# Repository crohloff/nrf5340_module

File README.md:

# nRF5340 module
WIP

## features
- power path management (USB or battery connected)
- battery charging circuit 500mA charging current
- no expensive uVias

## board front

## board back

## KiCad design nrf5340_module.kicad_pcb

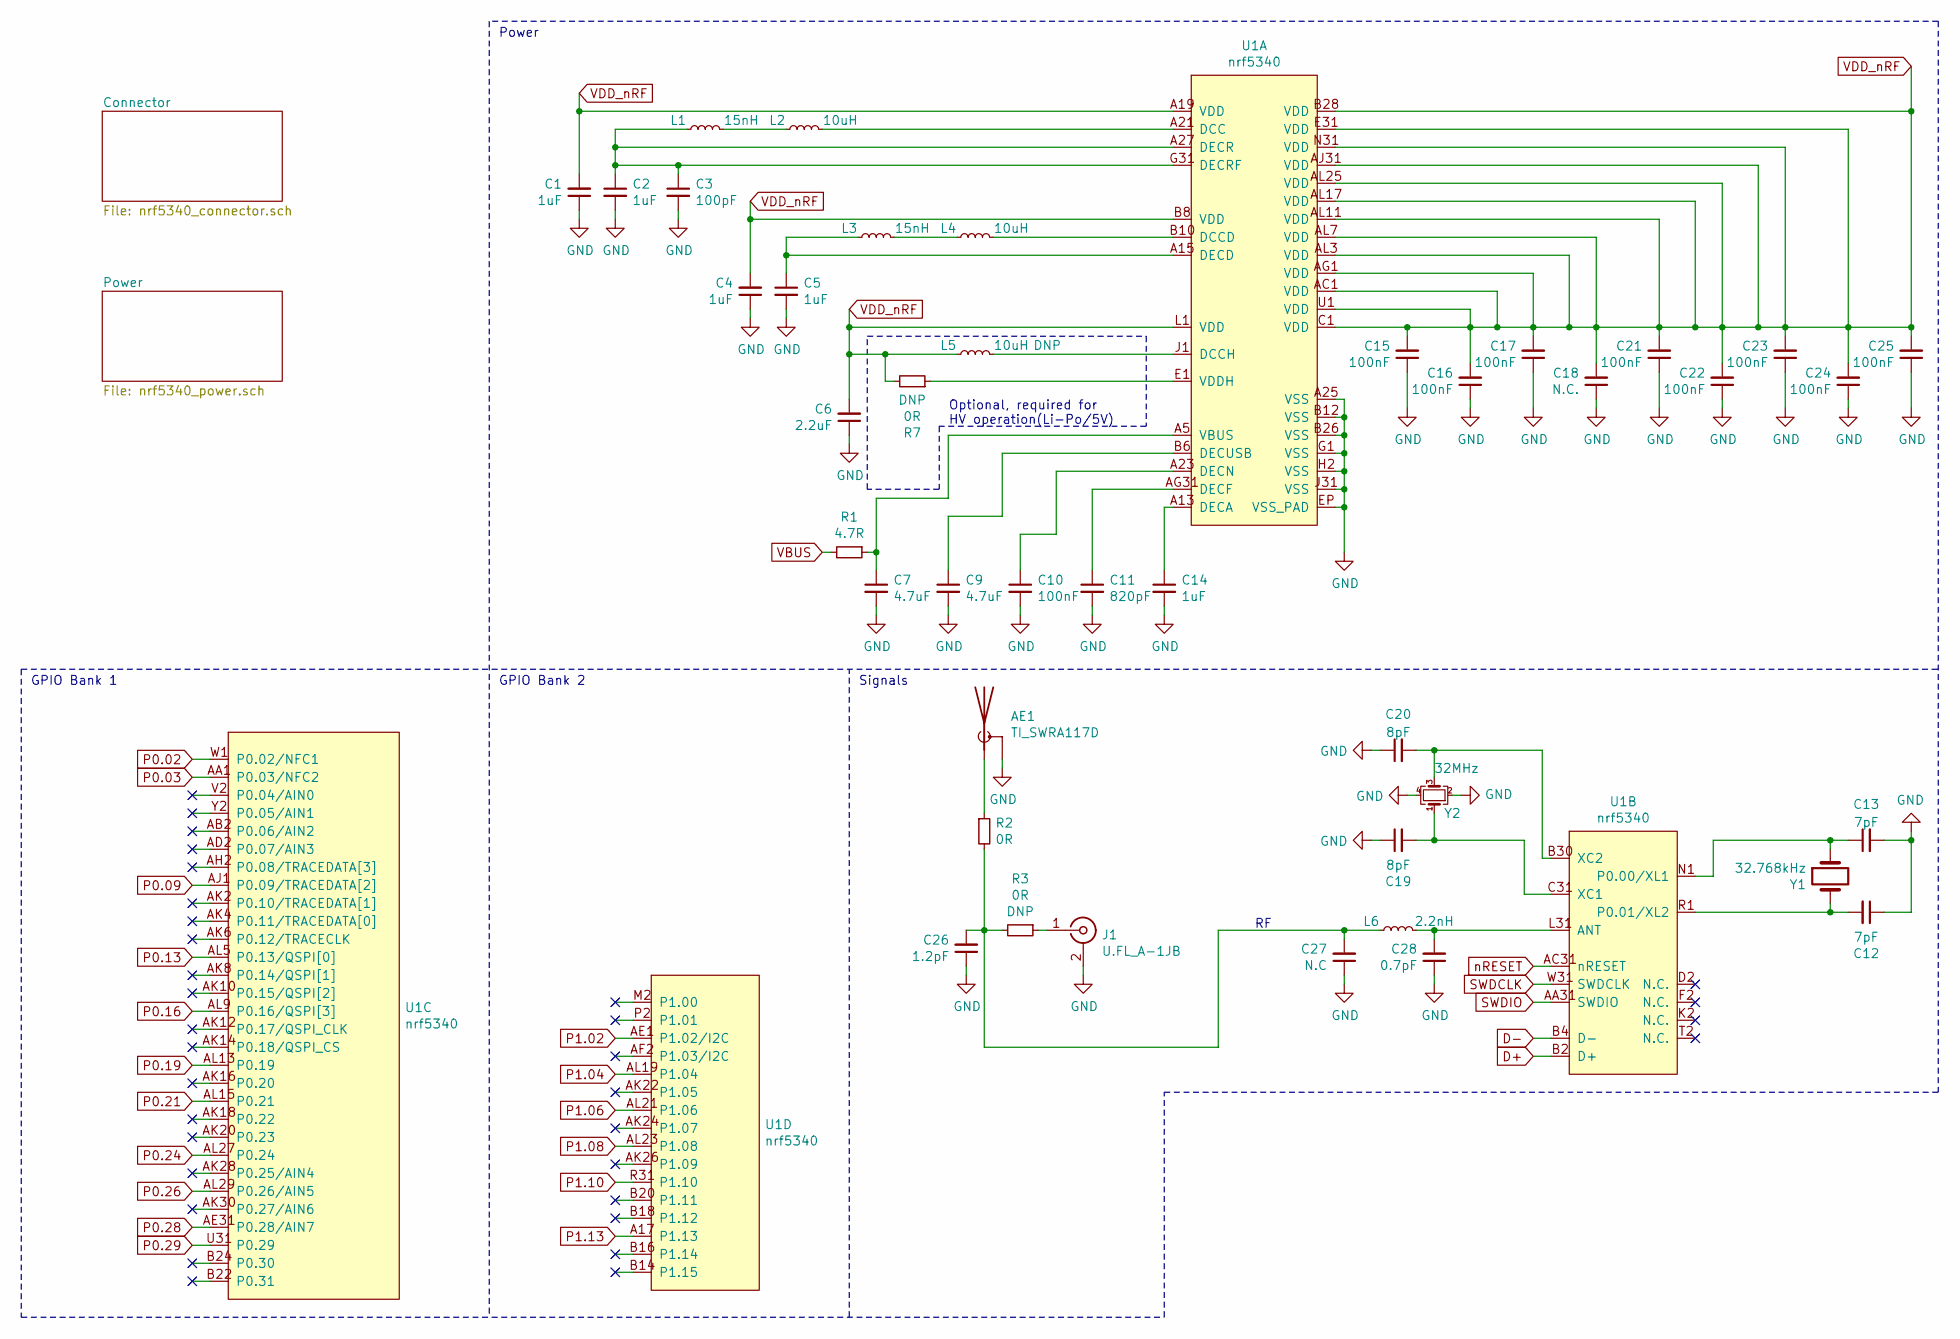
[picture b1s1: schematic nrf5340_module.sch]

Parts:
AE1: TI_SWRA117D; Texas_SWRA117D_2.4GHz_Right
C1, C2, C4, C5, C14: 1uF; C_0402_1005Metric
C3: 100pF; C_0201_0603Metric
C6: 2.2uF; C_0603_1608Metric
C7, C9: 4.7uF; C_0603_1608Metric
C10, C15, C16, C17, C21, C22, C23, C24, C25: 100nF; C_0201_0603Metric
C11: 820pF; C_0201_0603Metric
C12, C13: 7pF; C_0201_0603Metric
C18: N.C.; C_0201_0603Metric
C19, C20: 8pF; C_0201_0603Metric
C26: 1.2pF; C_0201_0603Metric
C27: N.C; C_0201_0603Metric
C28: 0.7pF; C_0201_0603Metric
J1: U.FL_A-1JB; CON_AMP_A-1JB
L1, L3: 15nH; L_0201_0603Metric
L2, L4, L5: 10uH; L_0603_1608Metric
L6: 2.2nH; L_0201_0603Metric
R1: 4.7R; R_0201_0603Metric
R2, R3: 0R; R_0201_0603Metric
R7: 0R; R_0603_1608Metric
U1: nrf5340; Nordic_AQFN-94-1EP_7x7mm_P0.4mm
Y1: 32.768kHz; Crystal_SMD_2012-2Pin_2.0x1.2mm
Y2: 32MHz; Crystal_SMD_2016-4Pin_2.0x1.6mm

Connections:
D+: U1.B2 (D+); also elsewhere on the board
D-: U1.B4 (D-); also elsewhere on the board
GND: AE1.2 (Shield), C1.1, C2.2, C3.2, C4.1, C5.2, C6.1, C7.2, C9.2, C10.2, C11.2, C12.1, C13.2, C14.2, C15.1, C16.1, C17.1, C18.1, C19.1, C20.1, C21.1, C22.1, C23.1, C24.1, C25.1, C26.1, C27.1, C28.1, J1.2 (Ext), U1.A25 (VSS), U1.B12 (VSS), U1.B26 (VSS), U1.EP (VSS_PAD), U1.G1 (VSS), U1.H2 (VSS), U1.J31 (VSS), Y2.2, Y2.4; also elsewhere on the board
unnamed: AE1.1 (A), R2.1
unnamed: C2.1, C3.1, L1.1, U1.A27 (DECR), U1.G31 (DECRF)
unnamed: C5.1, L3.1, U1.A15 (DECD)
unnamed: C7.1, R1.1, U1.A5 (VBUS)
unnamed: C9.1, U1.B6 (DECUSB)
unnamed: C10.1, U1.A23 (DECN)
unnamed: C11.1, U1.AG31 (DECF)
unnamed: C12.2, U1.R1 (P0.01/XL2), Y1.2
unnamed: C13.1, U1.N1 (P0.00/XL1), Y1.1
unnamed: C14.1, U1.A13 (DECA)
unnamed: C19.2, U1.C31 (XC1), Y2.1
unnamed: C20.2, U1.B30 (XC2), Y2.3
unnamed: C26.2, C27.2, L6.1, R2.2, R3.2
unnamed: C28.2, L6.2, U1.L31 (ANT)
unnamed: J1.1 (In), R3.1
unnamed: L1.2, L2.1
unnamed: L2.2, U1.A21 (DCC)
unnamed: L3.2, L4.1
unnamed: L4.2, U1.B10 (DCCD)
unnamed: L5.2, U1.J1 (DCCH)
unnamed: R7.1, U1.E1 (VDDH)
P0.02: U1.W1 (P0.02/NFC1); also elsewhere on the board
P0.03: U1.AA1 (P0.03/NFC2); also elsewhere on the board
P0.09: U1.AJ1 (P0.09/TRACEDATA[2]); also elsewhere on the board
P0.13: U1.AL5 (P0.13/QSPI[0]); also elsewhere on the board
P0.16: U1.AL9 (P0.16/QSPI[3]); also elsewhere on the board
P0.19: U1.AL13 (P0.19); also elsewhere on the board
P0.21: U1.AL15 (P0.21); also elsewhere on the board
P0.24: U1.AL27 (P0.24); also elsewhere on the board
P0.26: U1.AL29 (P0.26/AIN5); also elsewhere on the board
P0.28: U1.AE31 (P0.28/AIN7); also elsewhere on the board
P0.29: U1.U31 (P0.29); also elsewhere on the board
P1.02: U1.AE1 (P1.02/I2C); also elsewhere on the board
P1.04: U1.AL19 (P1.04); also elsewhere on the board
P1.06: U1.AL21 (P1.06); also elsewhere on the board
P1.08: U1.AL23 (P1.08); also elsewhere on the board
P1.10: U1.R31 (P1.10); also elsewhere on the board
P1.13: U1.A17 (P1.13); also elsewhere on the board
SWDCLK: U1.W31 (SWDCLK); also elsewhere on the board
SWDIO: U1.AA31 (SWDIO); also elsewhere on the board
VBUS: R1.2; also elsewhere on the board
VDD_nRF: C1.2, C4.2, C6.2, C15.2, C16.2, C17.2, C18.2, C21.2, C22.2, C23.2, C24.2, C25.2, L5.1, R7.2, U1.A19 (VDD), U1.AC1 (VDD), U1.AG1 (VDD), U1.AJ31 (VDD), U1.AL3 (VDD), U1.AL7 (VDD), U1.AL11 (VDD), U1.AL17 (VDD), U1.AL25 (VDD), U1.B8 (VDD), U1.B28 (VDD), U1.C1 (VDD), U1.E31 (VDD), U1.L1 (VDD), U1.N31 (VDD), U1.U1 (VDD); also elsewhere on the board
nRESET: U1.AC31 (nRESET); also elsewhere on the board

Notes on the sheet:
Optional, required for HV operation(Li-Po/5V)
GPIO Bank 1
GPIO Bank 2
Power
Signals

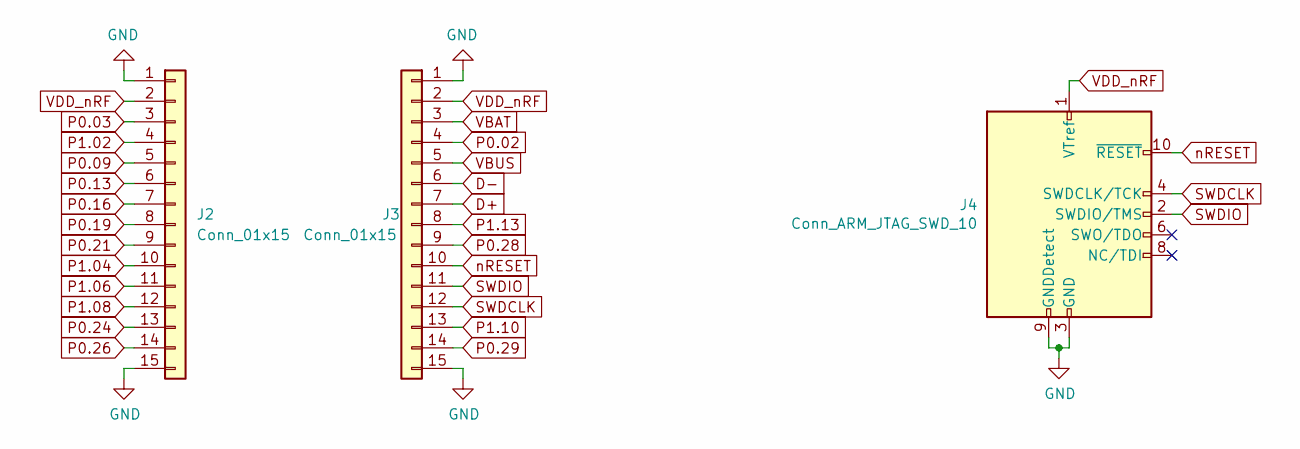
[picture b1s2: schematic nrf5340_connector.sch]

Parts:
J2, J3: Conn_01x15; PinHeader_1x15_P1.27mm_Vertical
J4: Conn_ARM_JTAG_SWD_10; PinHeader_2x05_P1.27mm_Vertical_SMD

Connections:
D+: J3.7; also elsewhere on the board
D-: J3.6; also elsewhere on the board
GND: J2.1, J2.15, J3.1, J3.15, J4.3 (GND), J4.5 (GND), J4.9 (GNDDetect); also elsewhere on the board
P0.02: J3.4; also elsewhere on the board
P0.03: J2.3; also elsewhere on the board
P0.09: J2.5; also elsewhere on the board
P0.13: J2.6; also elsewhere on the board
P0.16: J2.7; also elsewhere on the board
P0.19: J2.8; also elsewhere on the board
P0.21: J2.9; also elsewhere on the board
P0.24: J2.13; also elsewhere on the board
P0.26: J2.14; also elsewhere on the board
P0.28: J3.9; also elsewhere on the board
P0.29: J3.14; also elsewhere on the board
P1.02: J2.4; also elsewhere on the board
P1.04: J2.10; also elsewhere on the board
P1.06: J2.11; also elsewhere on the board
P1.08: J2.12; also elsewhere on the board
P1.10: J3.13; also elsewhere on the board
P1.13: J3.8; also elsewhere on the board
SWDCLK: J3.12, J4.4 (SWDCLK/TCK); also elsewhere on the board
SWDIO: J3.11, J4.2 (SWDIO/TMS); also elsewhere on the board
VBAT: J3.3; also elsewhere on the board
VBUS: J3.5; also elsewhere on the board
VDD_nRF: J2.2, J3.2, J4.1 (VTref); also elsewhere on the board
nRESET: J3.10, J4.10 (~RESET~); also elsewhere on the board

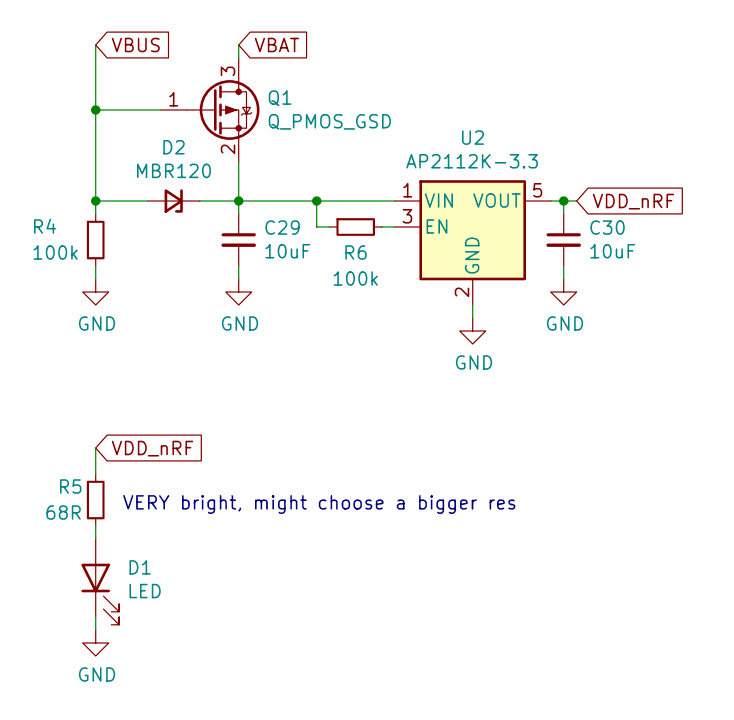
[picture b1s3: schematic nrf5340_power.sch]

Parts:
C29, C30: 10uF; C_0201_0603Metric
D1: LED; LED_0402_1005Metric
D2: MBR120; D_SOD-123
Q1: Q_PMOS_GSD; SOT-23
R4, R6: 100k; R_0201_0603Metric
R5: 68R; R_0201_0603Metric
U2: AP2112K-3.3; SOT-23-5

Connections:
GND: C29.2, C30.2, D1.1 (K), R4.2, U2.2 (GND); also elsewhere on the board
unnamed: C29.1, D2.1 (K), Q1.2 (S), R6.1, U2.1 (VIN)
unnamed: D1.2 (A), R5.2
unnamed: R6.2, U2.3 (EN)
VBAT: Q1.3 (D); also elsewhere on the board
VBUS: D2.2 (A), Q1.1 (G), R4.1; also elsewhere on the board
VDD_nRF: C30.1, R5.1, U2.5 (VOUT); also elsewhere on the board

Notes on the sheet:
VERY bright, might choose a bigger res

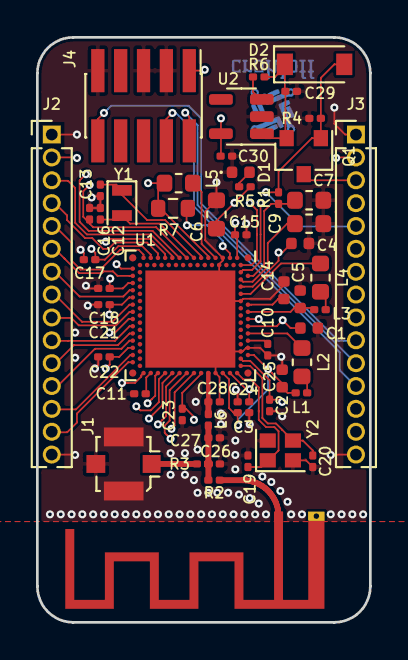
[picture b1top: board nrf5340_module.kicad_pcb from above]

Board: 4 copper layers, 18.5 x 32.5 mm, 54 parts (0 on the bottom side), 50 nets.

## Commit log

2019-11-17 readme / gitignore
2019-11-17 nrf5340 module init
2019-11-20 first rev pcb without impedance matching
2019-11-21 fix traces underneath nrf gnd pad and VDD_HV
2019-11-21 fix vdd_hv
2019-11-22 fix vddh stuff
2020-01-15 added keepout, stitching, switched layers for better impedance matching
2021-02-10 update license/docs
